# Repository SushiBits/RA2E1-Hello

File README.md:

# ra2e1-hello

A bare-metal demo for the Renesas RA2E1 (Cortex-M23), built **without
e² studio and without the Flexible Software Package (FSP)**. Just a Makefile,
the GNU Arm toolchain, CMSIS 6 and the device headers generated from the
Renesas SVD.

The firmware starts the 24 MHz HSE crystal, programs SysTick for a 1 ms
timebase and blinks the LED on P201 every 500 ms.

This is my first project on a Renesas MCU, and my first Cortex-M23 project
that produced blinkenlights.

## Hardware

The board is in [hardware/](hardware) as a KiCad 8 project (schematic, PCB
and project settings), and the same design is published as
[doc/ra2e1-evk.pdf](doc/ra2e1-evk.pdf). It is built around an
R7FA2E1AxxxFJ (LQFP-32), a 24 MHz crystal, a USB-C connector, one LED on P201
and one button.

The physical board carries an **R7FA2E1A5** (32 KB flash). The A5, A7 and A9
parts differ only in flash size (32, 64 and 128 KB, all with the same 16 KB
of RAM and the same peripherals), so one device header and one SVD cover the
family: the build links the 32 KB memory map from
`contrib/platform/lib/R7FA2E1A5.ld`, while the debug configuration and the
SVD name the A9. The mismatch is intentional, not a copy-paste slip.

Renesas documentation lives in [doc/vendor/](doc/vendor).

## Repository layout

| Path | Contents |
|---|---|
| `src/` | Application: `main.c`, `systick.c`, `config.c` (option bytes) |
| `include/` | Project headers, e.g. `systick.h` |
| `lib/ra2e1-hello.ld` | Project linker script (vector table, `.config`, layout) |
| `contrib/platform/` | Device support: startup code, system file, RA2E1 memory maps, SVD/SFR/SFD sources |
| `contrib/platform/include/` | Device headers, generated from the SVD by `make headers` |
| `contrib/cmsis/` | CMSIS 6 submodule |
| `hardware/` | KiCad project for the board |
| `doc/` | Board schematics; `doc/vendor/` holds the Renesas datasheet and manuals |
| `.vscode/` | Build task and Cortex-Debug (J-Link) configuration |

## Building

Requirements:

- `arm-none-eabi-gcc` with Cortex-M23 support (built here with Arm GNU Toolchain 13.2 and 15.3)
- GNU make, plus a Unix-like shell for `mkdir -p` and `rm -rf` (Git Bash or MSYS2)
- `python3` (generates the interrupt handler table with `contrib/platform/share/irqn.py`)
- Optionally Keil's `SVDConv.exe` in `C:\Keil_v5\UV4` (or edit `SVDCONV_PATH` in the
  Makefile) to regenerate the device headers from the SVD

```sh
make            # build ra2e1-hello.elf
make hex        # Intel HEX
make bin        # raw binary
make size       # Berkeley totals and a per-section breakdown
make clean      # remove build products
make distclean  # also remove generated device headers
```

The header generation step is prefixed with `-` in the Makefile, so a missing
`SVDConv.exe` does not break the build; the checked-in headers are used
instead.

## Debugging

`.vscode/launch.json` runs Cortex-Debug against a J-Link over SWD, erases the
flash before programming, and loads `contrib/platform/share/R7FA2E1A9.svd` so
the peripheral registers show up by name.

## Notes on the RA2E1

**Write protection is scattered.** Almost every peripheral has its own
write-protect register somewhere in its register block, and you only find out
you forgot one when the write silently does nothing. The centralised
enable/reset scheme used by STM32 and friends is simply easier to understand.

**TrustZone is optional here, thankfully.** Renesas did not go all in on
TrustZone for this part, so there is no security state to get past before the
first instruction runs. My first Cortex-M23 project, on an ATSAML11, crashed
and burned for exactly that reason: the code never managed to run past the
TrustZone level.

**Option bytes in the middle of flash are a trap.** The option-setting memory
sits at `0x00000400`, so the first kilobyte of flash is dead space on small
parts and the linker script has to work around it. Pinning the `.config`
section there took a bit of linker-script wizardry: a bare `. = 0x00000400`
does not move a section that is assigned to a memory region, so the address
has to be attached to the section itself (see `lib/ra2e1-hello.ld`). It is a
common stumbling block for newcomers, and one that fails silently.

## Licence

BSD 3-Clause, see [LICENSE.md](LICENSE.md).
Copyright &copy; 2018-2026 HIKARU Infotech Shanghai Ltd.

Third-party material keeps its own terms:

- Everything under `doc/vendor/` is copyright Renesas Electronics.
- `contrib/platform/share/R7FA2E1A9.sfd`, `R7FA2E1A9.SFR` and
  `R7FA2E1A9.svd` are copyright Renesas, with my own edits.

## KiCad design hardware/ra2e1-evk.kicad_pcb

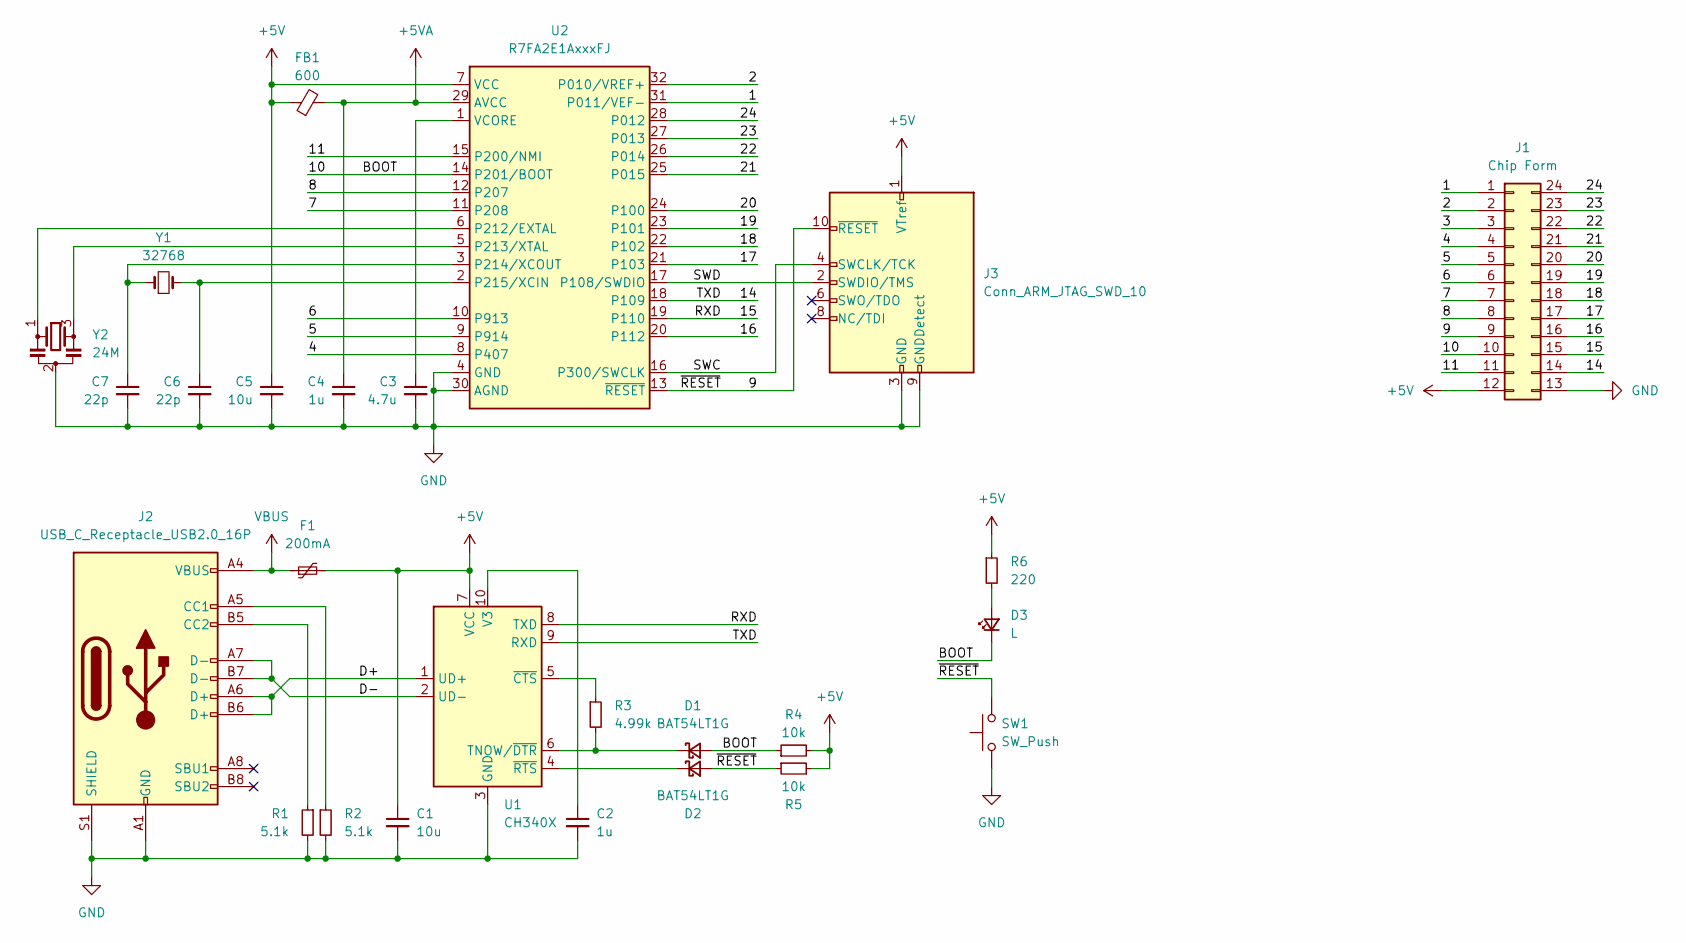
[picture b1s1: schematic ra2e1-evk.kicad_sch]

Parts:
C1, C5: 10u; C_0603_1608Metric_Pad1.08x0.95mm_HandSolder
C2, C4: 1u; C_0603_1608Metric_Pad1.08x0.95mm_HandSolder
C3: 4.7u; C_0603_1608Metric_Pad1.08x0.95mm_HandSolder
C6, C7: 22p; C_0603_1608Metric_Pad1.08x0.95mm_HandSolder
D1, D2: BAT54LT1G; D_SOD-323
D3: L; LED_0805_2012Metric_Pad1.15x1.40mm_HandSolder
F1: 200mA; Fuse_0805_2012Metric_Pad1.15x1.40mm_HandSolder
FB1: 600; L_0603_1608Metric_Pad1.05x0.95mm_HandSolder
J1: Chip Form; DIP-24_W15.24mm
J2: USB_C_Receptacle_USB2.0_16P; USB_C_Receptacle_HRO_TYPE-C-31-M-12
J3: Conn_ARM_JTAG_SWD_10; PinHeader_2x05_P1.27mm_Vertical_SMD
R1, R2: 5.1k; R_0603_1608Metric_Pad0.98x0.95mm_HandSolder
R3: 4.99k; R_0603_1608Metric_Pad0.98x0.95mm_HandSolder
R4, R5: 10k; R_0603_1608Metric_Pad0.98x0.95mm_HandSolder
R6: 220; R_0603_1608Metric_Pad0.98x0.95mm_HandSolder
SW1: SW_Push; SW_SPST_B3U-1000P
U1: CH340X; MSOP-10_3x3mm_P0.5mm
U2: R7FA2E1AxxxFJ; LQFP-32_7x7mm_P0.8mm
Y1: 32768; Crystal_SMD_3215-2Pin_3.2x1.5mm
Y2: 24M; Resonator_SMD_Murata_CSTxExxV-3Pin_3.0x1.1mm

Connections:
+5V: C1.1, C5.1, F1.2, FB1.1, J1.12, J3.1 (VTref), R4.2, R5.2, R6.1, U1.7 (VCC), U2.7 (VCC)
+5VA: C4.1, FB1.2, U2.29 (AVCC)
/1: J1.1, U2.31 (P011/VEF-)
/2: J1.2, U2.32 (P010/VREF+)
/3: J1.3
/4: J1.4, U2.8 (P407)
/5: J1.5, U2.9 (P914)
/6: J1.6, U2.10 (P913)
/7: J1.7, U2.11 (P208)
/8: J1.8, U2.12 (P207)
/9: D2.2 (A), J1.9, J3.10 (~RESET), R5.1, SW1.2, U2.13 (~RESET)
/10: D1.2 (A), D3.1 (K), J1.10, R4.1, U2.14 (P201/BOOT)
/11: J1.11, U2.15 (P200/NMI)
/14: J1.14, U1.9 (RXD), U2.18 (P109)
/15: J1.15, U1.8 (TXD), U2.19 (P110)
/16: J1.16, U2.20 (P112)
/17: J1.17, U2.21 (P103)
/18: J1.18, U2.22 (P102)
/19: J1.19, U2.23 (P101)
/20: J1.20, U2.24 (P100)
/21: J1.21, U2.25 (P015)
/22: J1.22, U2.26 (P014)
/23: J1.23, U2.27 (P013)
/24: J1.24, U2.28 (P012)
/D+: J2.A6 (D+), J2.B6 (D+), U1.1 (UD+)
/D-: J2.A7 (D-), J2.B7 (D-), U1.2 (UD-)
/SWC: J3.4 (SWCLK/TCK), U2.16 (P300/SWCLK)
/SWD: J3.2 (SWDIO/TMS), U2.17 (P108/SWDIO)
GND: C1.2, C2.2, C3.2, C4.2, C5.2, C6.2, C7.2, J1.13, J2.A1 (GND), J2.A12 (GND), J2.B1 (GND), J2.B12 (GND), J2.S1 (SHIELD), J3.3 (GND), J3.5 (GND), J3.9 (GNDDetect), R1.2, R2.2, SW1.1, U1.3 (GND), U2.4 (GND), U2.30 (AGND), Y2.2
unnamed: D1.1 (K), R3.2, U1.6 (TNOW/~DTR)
unnamed: D2.1 (K), U1.4 (~RTS)
unnamed: D3.2 (A), R6.2
unnamed: J2.A5 (CC1), R2.1
unnamed: J2.B5 (CC2), R1.1
unnamed: C2.1, U1.10 (V3)
unnamed: R3.1, U1.5 (~CTS)
unnamed: U2.6 (P212/EXTAL), Y2.1
unnamed: U2.5 (P213/XTAL), Y2.3
unnamed: C7.1, U2.3 (P214/XCOUT), Y1.1
unnamed: C6.1, U2.2 (P215/XCIN), Y1.2
unnamed: C3.1, U2.1 (VCORE)
VBUS: F1.1, J2.A4 (VBUS), J2.A9 (VBUS), J2.B4 (VBUS), J2.B9 (VBUS)

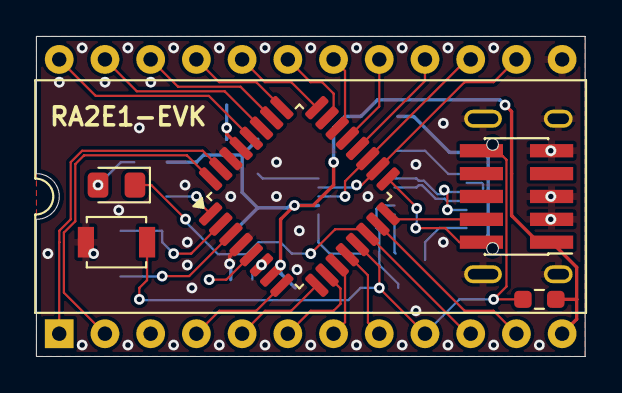
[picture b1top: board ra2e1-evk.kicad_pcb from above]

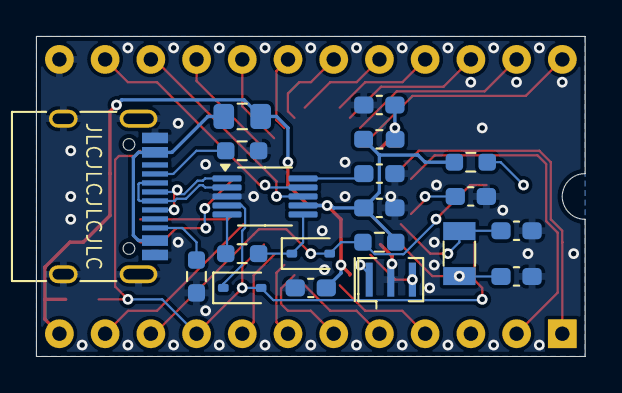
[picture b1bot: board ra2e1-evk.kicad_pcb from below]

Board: 2 copper layers, 30.5 x 17.8 mm, 26 parts (20 on the bottom side), 41 nets.
